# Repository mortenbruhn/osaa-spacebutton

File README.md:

# osaa-spacebutton
A WEMOS (D1 mini / [ESP8266](https://github.com/esp8266/Arduino)) based button to interface the [Open Space Aarhus](https://github.com/openspaceaarhus) [SpaceAPI](https://github.com/spaceapi).

There is also a PCB layouted in [KiCAD](http://kicad-pcb.org/).

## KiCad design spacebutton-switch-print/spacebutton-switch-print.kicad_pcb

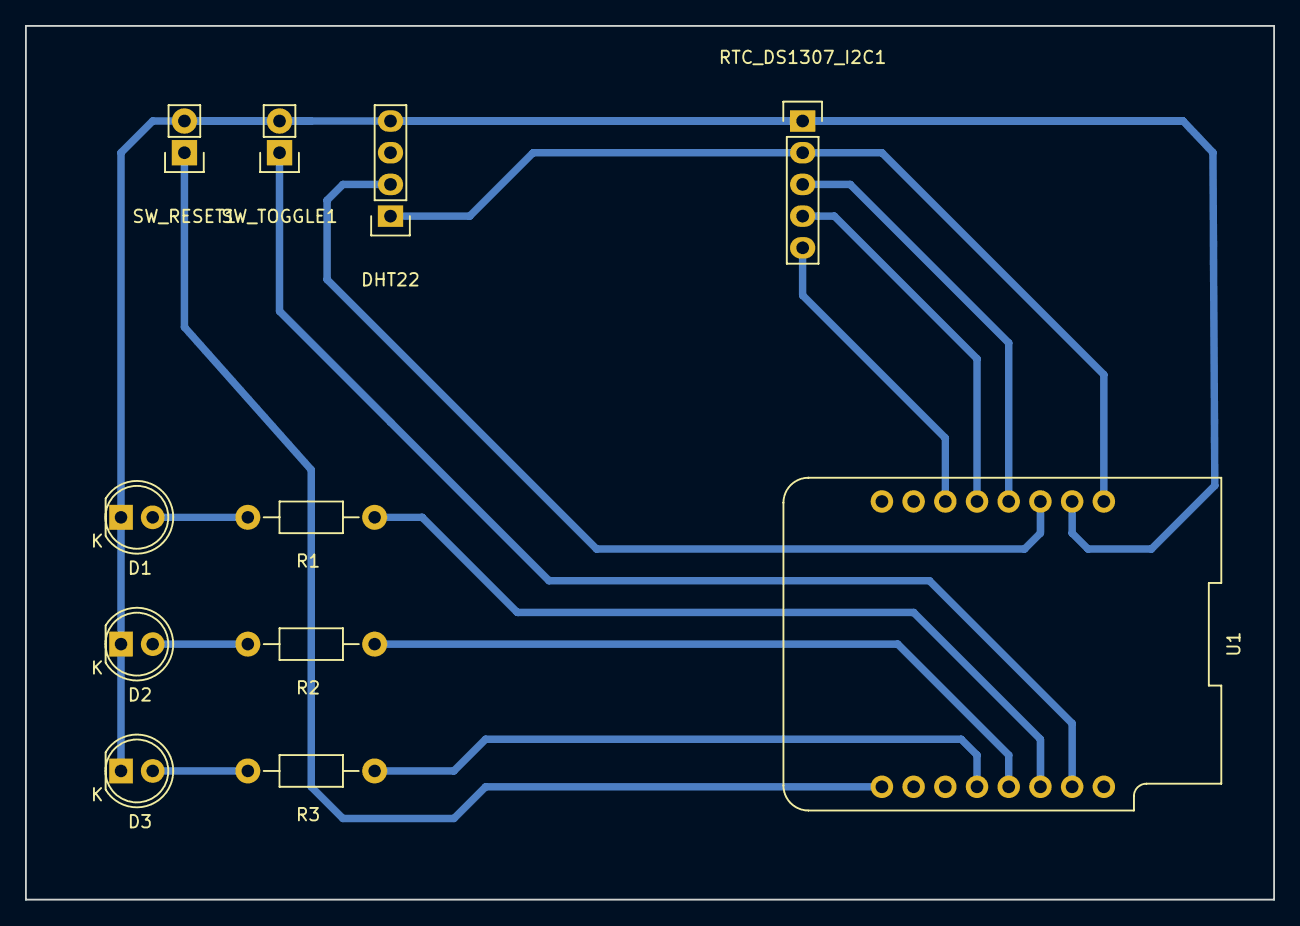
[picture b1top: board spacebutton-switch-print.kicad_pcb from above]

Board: 2 copper layers, 100.0 x 70.0 mm, 11 parts (0 on the bottom side), 14 nets.

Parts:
D1: RED; LED-5MM
D2: YELLOW; LED-5MM
D3: GREEN; LED-5MM
DHT22: CONN_01X04; Pin_Header_Straight_1x04
R1, R2, R3: R; Resistor_Horizontal_RM10mm
RTC_DS1307_I2C1: CONN_01X05; Pin_Header_Straight_1x05
SW_RESET1: SW_PUSH; Pin_Header_Straight_1x02
SW_TOGGLE1: SW_PUSH; Pin_Header_Straight_1x02
U1: WeMos_mini; wemos-d1-mini-with-pin-header

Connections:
unnamed: D1.1, D2.1, D3.1, DHT22.4, RTC_DS1307_I2C1.1, SW_RESET1.2, SW_TOGGLE1.2, U1.2
unnamed: D1.2, R1.2
unnamed: D2.2, R2.2
unnamed: D3.2, R3.2
unnamed: DHT22.1, RTC_DS1307_I2C1.2, U1.1
unnamed: DHT22.2, U1.3
unnamed: R1.1, U1.14
unnamed: R2.1, U1.13
unnamed: R3.1, U1.12
unnamed: RTC_DS1307_I2C1.3, U1.4
unnamed: RTC_DS1307_I2C1.4, U1.5
unnamed: RTC_DS1307_I2C1.5, U1.6
unnamed: SW_RESET1.1, U1.9
unnamed: SW_TOGGLE1.1, U1.15

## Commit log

2018-01-25 Initial commit of Arduino code
2018-04-19 Changed sketch to match pin IO on PCB layout
2018-04-19 Moved Arduino files to own folder
2018-04-19 Added KiCAD files
2018-04-19 Added script to generate G-code from Gerber files
2018-04-19 Added SVG file for plexiglass front
2018-04-19 Arduino: Added debug to sketch
2018-11-01 Added code to reset if Wifi connection fails for extended periods of time.
2018-11-04 Removed directly imported wemos-d1-mini-kicad repo
2018-11-04 Added directory wemos-d1-mini-kicad as submodule
2019-10-01 Changed pin for detonator
2023-01-05 Don't remember where I was going with this...
2023-01-05 Fixed SpaceButton for new OSAA at OPA
2023-01-05 Try 60 times before resetting
2023-01-05 Cleanup
